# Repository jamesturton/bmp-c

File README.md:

# Black Magic Probe v2.1 USB-C version

[![CC BY-SA 4.0][cc-by-sa-shield]][cc-by-sa]

This version of the Black Magic Probe is based of v2.1 and has been updated for use in 2020 with a USB type C connector.
The design is functionally the same as v2.1, but simply with a new connector.

## Known issues
### Schematic
 - 
### Layout
 - 

[cc-by-sa]: http://creativecommons.org/licenses/by-sa/4.0/
[cc-by-sa-shield]: https://img.shields.io/badge/License-CC%20BY--SA%204.0-lightgrey.svg

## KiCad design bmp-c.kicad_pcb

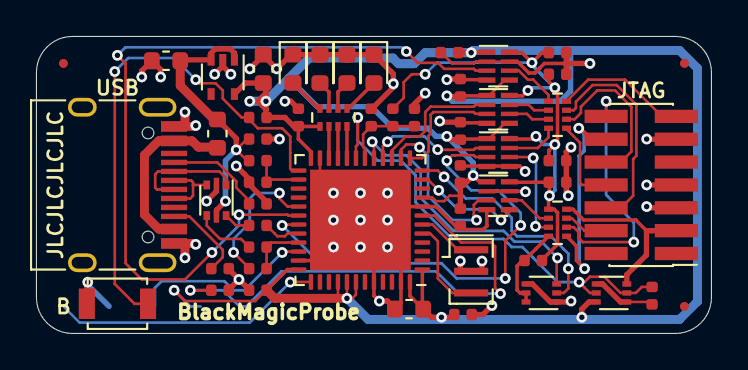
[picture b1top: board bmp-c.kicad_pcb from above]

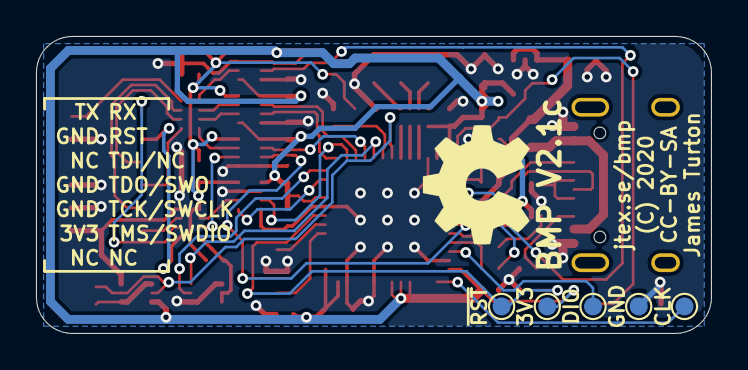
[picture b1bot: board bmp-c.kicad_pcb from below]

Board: 2 copper layers, 37.5 x 16.5 mm, 60 parts (6 on the bottom side), 55 nets.

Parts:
C1, C4, C5, C6, C8, C9, C11, C12, C13, C15, C16, C17, C18, C19, C20: 100n; C_0402_1005Metric
C3, C7, C21: 4u7; C_0603_1608Metric
D1: LED RED; LED_0603_1608Metric
D2: LED BLUE; LED_0603_1608Metric
D3: LED GREEN; LED_0603_1608Metric
D4: LED YELLOW; LED_0603_1608Metric
FB1: 330R @ 100MHz; Fuse_0603_1608Metric
FID1, FID2, FID3: Fiducial; Fiducial_0.5mm_Mask1.5mm
J1: TYPE-C-31-M-12; USB_C_Receptacle_HRO_TYPE-C-31-M-12
J3: FTSH-107-01-F-DV-K; PinHeader_2x07_P1.27mm_Vertical_SMD
LOGO1: Logo_Open_Hardware_Small; OSHW-Symbol_6.7x6mm_SilkScreen
Q1: DMG1023UV; SOT-563
Q2: DMG1024UV; SOT-563
R1, R2: 5k1; R_0402_1005Metric
R3, R7, R8, R11, R12: 10k; R_0402_1005Metric
R4, R9: 4k7; R_0402_1005Metric
R5, R6: 22R; R_0402_1005Metric
R10: 1k5; R_0402_1005Metric
RN1: 330R; R_Array_Convex_4x0402
RN2, RN3: 100R; R_Array_Convex_4x0402
SW1: B3U-1000P; SW_SPST_B3U-1000P
TP1: 3V3; TestPoint_Pad_D1.0mm
TP2: GND; TestPoint_Pad_D1.0mm
TP4: ~RST; TestPoint_Pad_D1.0mm
TP5: SWDIO; TestPoint_Pad_D1.0mm
TP6: SWCLK; TestPoint_Pad_D1.0mm
U1: USBLC6-2P6; SOT-666
U2, U3, U4, U5: 74LVC2T45GT; X2SON-8_1.95x1mm_P0.5mm
U6: STM32F103CBU; QFN-48-1EP_7x7mm_P0.5mm_EP5.6x5.6mm
U7: TLV70033DCK; SOT-353_SC-70-5
Y1: CSTNE8M00G520000R0; Resonator_SMD_muRata_CSTxExxV-3Pin_3.0x1.1mm

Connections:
+3V3: C1.1, C3.1, C6.1, C9.1, C15.1, C16.2, C17.2, C18.2, C20.2, C21.2, Q1.6, R8.2, RN1.1, TP1.1, U2.1, U2.5, U3.1, U3.5, U4.1, U5.1, U6.1, U6.9, U6.24, U6.36, U6.40, U6.41, U6.42, U6.48, U7.5
+5V: C5.1, C7.1, FB1.1, R4.1, U1.5, U7.1, U7.3
/LED0: RN1.4, U6.20
/LED1: RN1.3, U6.21
/LED2: RN1.2, U6.22
/PWR_BR: Q1.2, Q1.5, R12.1, U6.19
/RST: J3.12, RN2.1
/RXD: J3.14, RN2.2
/SWCLK: TP6.1, U6.37
/SWDIO: TP5.1, U6.34
/TCK: J3.6, RN3.3
/TDI: J3.10, RN3.2
/TDO: J3.8, RN3.1
/TMS: J3.4, RN2.3
/TPWR: J3.3, Q1.3, RN2.4
/TXD: J3.13, RN3.4
/USBX_n: J1.A7, J1.B7, U1.1
/USBX_p: J1.A6, J1.B6, U1.3
/USBi_n: R5.1, U6.32
/USBi_p: R6.1, R10.1, U6.33
/VBUS: R3.1, R4.2, U6.26
/iRST: Q2.2, U6.12
/iRST_SENSE: Q2.3, U6.17
/iRXD: U4.3, U6.31
/iTCK: U3.2, U6.15
/iTDI: U3.3, U6.13
/iTDO: U4.2, U6.16
/iTMS: U5.3, U6.14
/iTMS_DIR: U5.5, U6.11
/iTPWR: C11.1, R7.1, R9.2, U6.18
/iTXD: U2.3, U6.30
/xRST: Q2.5, Q2.6, R11.1, RN2.8
/xRXD: RN2.7, U4.6
/xTCK: RN3.6, U3.7
/xTDI: RN3.7, U3.6
/xTDO: RN3.8, U4.7
/xTMS: RN2.6, U5.6
/xTPWR: C4.2, C8.2, C13.2, C19.2, R9.1, R11.2, RN2.5, U2.8, U3.8, U4.8, U5.8
/xTXD: RN3.5, U2.6
GND: C1.2, C3.2, C4.1, C5.2, C6.2, C7.2, C8.1, C9.2, C11.2, C12.2, C13.1, C15.2, C16.1, C17.1, C18.1, C19.1, C20.1, C21.1, D1.1, D2.1, D3.1, D4.1, J1.A1, J1.A12, J1.B1, J1.B12, J3.5, J3.7, J3.11, Q2.1, Q2.4, R1.1, R2.1, R3.2, R7.2, SW1.1, TP2.1, U1.2, U2.2, U2.4, U2.7, U3.4, U4.4, U4.5, U5.2, U5.4, U5.7, U6.8, U6.23, U6.35, U6.44, U6.47, U6.49, U7.2, Y1.2
unnamed: C12.1, TP4.1, U6.7
unnamed: D1.2, RN1.7
unnamed: D2.2, RN1.8
unnamed: D3.2, RN1.6
unnamed: D4.2, RN1.5
unnamed: FB1.2, J1.A4, J1.A9, J1.B4, J1.B9
unnamed: J1.A5, R1.2
unnamed: J1.B5, R2.2
unnamed: Q1.1, Q1.4, R12.2
unnamed: R5.2, U1.6
unnamed: R6.2, U1.4
unnamed: R8.1, SW1.2, U6.25
unnamed: R10.2, U6.29
unnamed: U6.5, Y1.3
unnamed: U6.6, Y1.1

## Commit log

2020-06-30 Inital commit.
2020-06-30 Added CC-BY-SA4.0 license.
2020-06-30 Added bmp-c-panel.kicad_pcb.
2020-06-30 Added PNG of 3D render and PDF of schematic.
2020-07-19 Fix up known issues.
2020-07-19 Add photo to README.md.
2020-07-21 Update alignment holes to be Stencil8 compatible.
2020-08-28 Moved panel alignment holes for easier assembly.

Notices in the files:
bmp-c.kicad_pcb:
(C) 2020 James Turton
License: CC-BY-SA 4.0
